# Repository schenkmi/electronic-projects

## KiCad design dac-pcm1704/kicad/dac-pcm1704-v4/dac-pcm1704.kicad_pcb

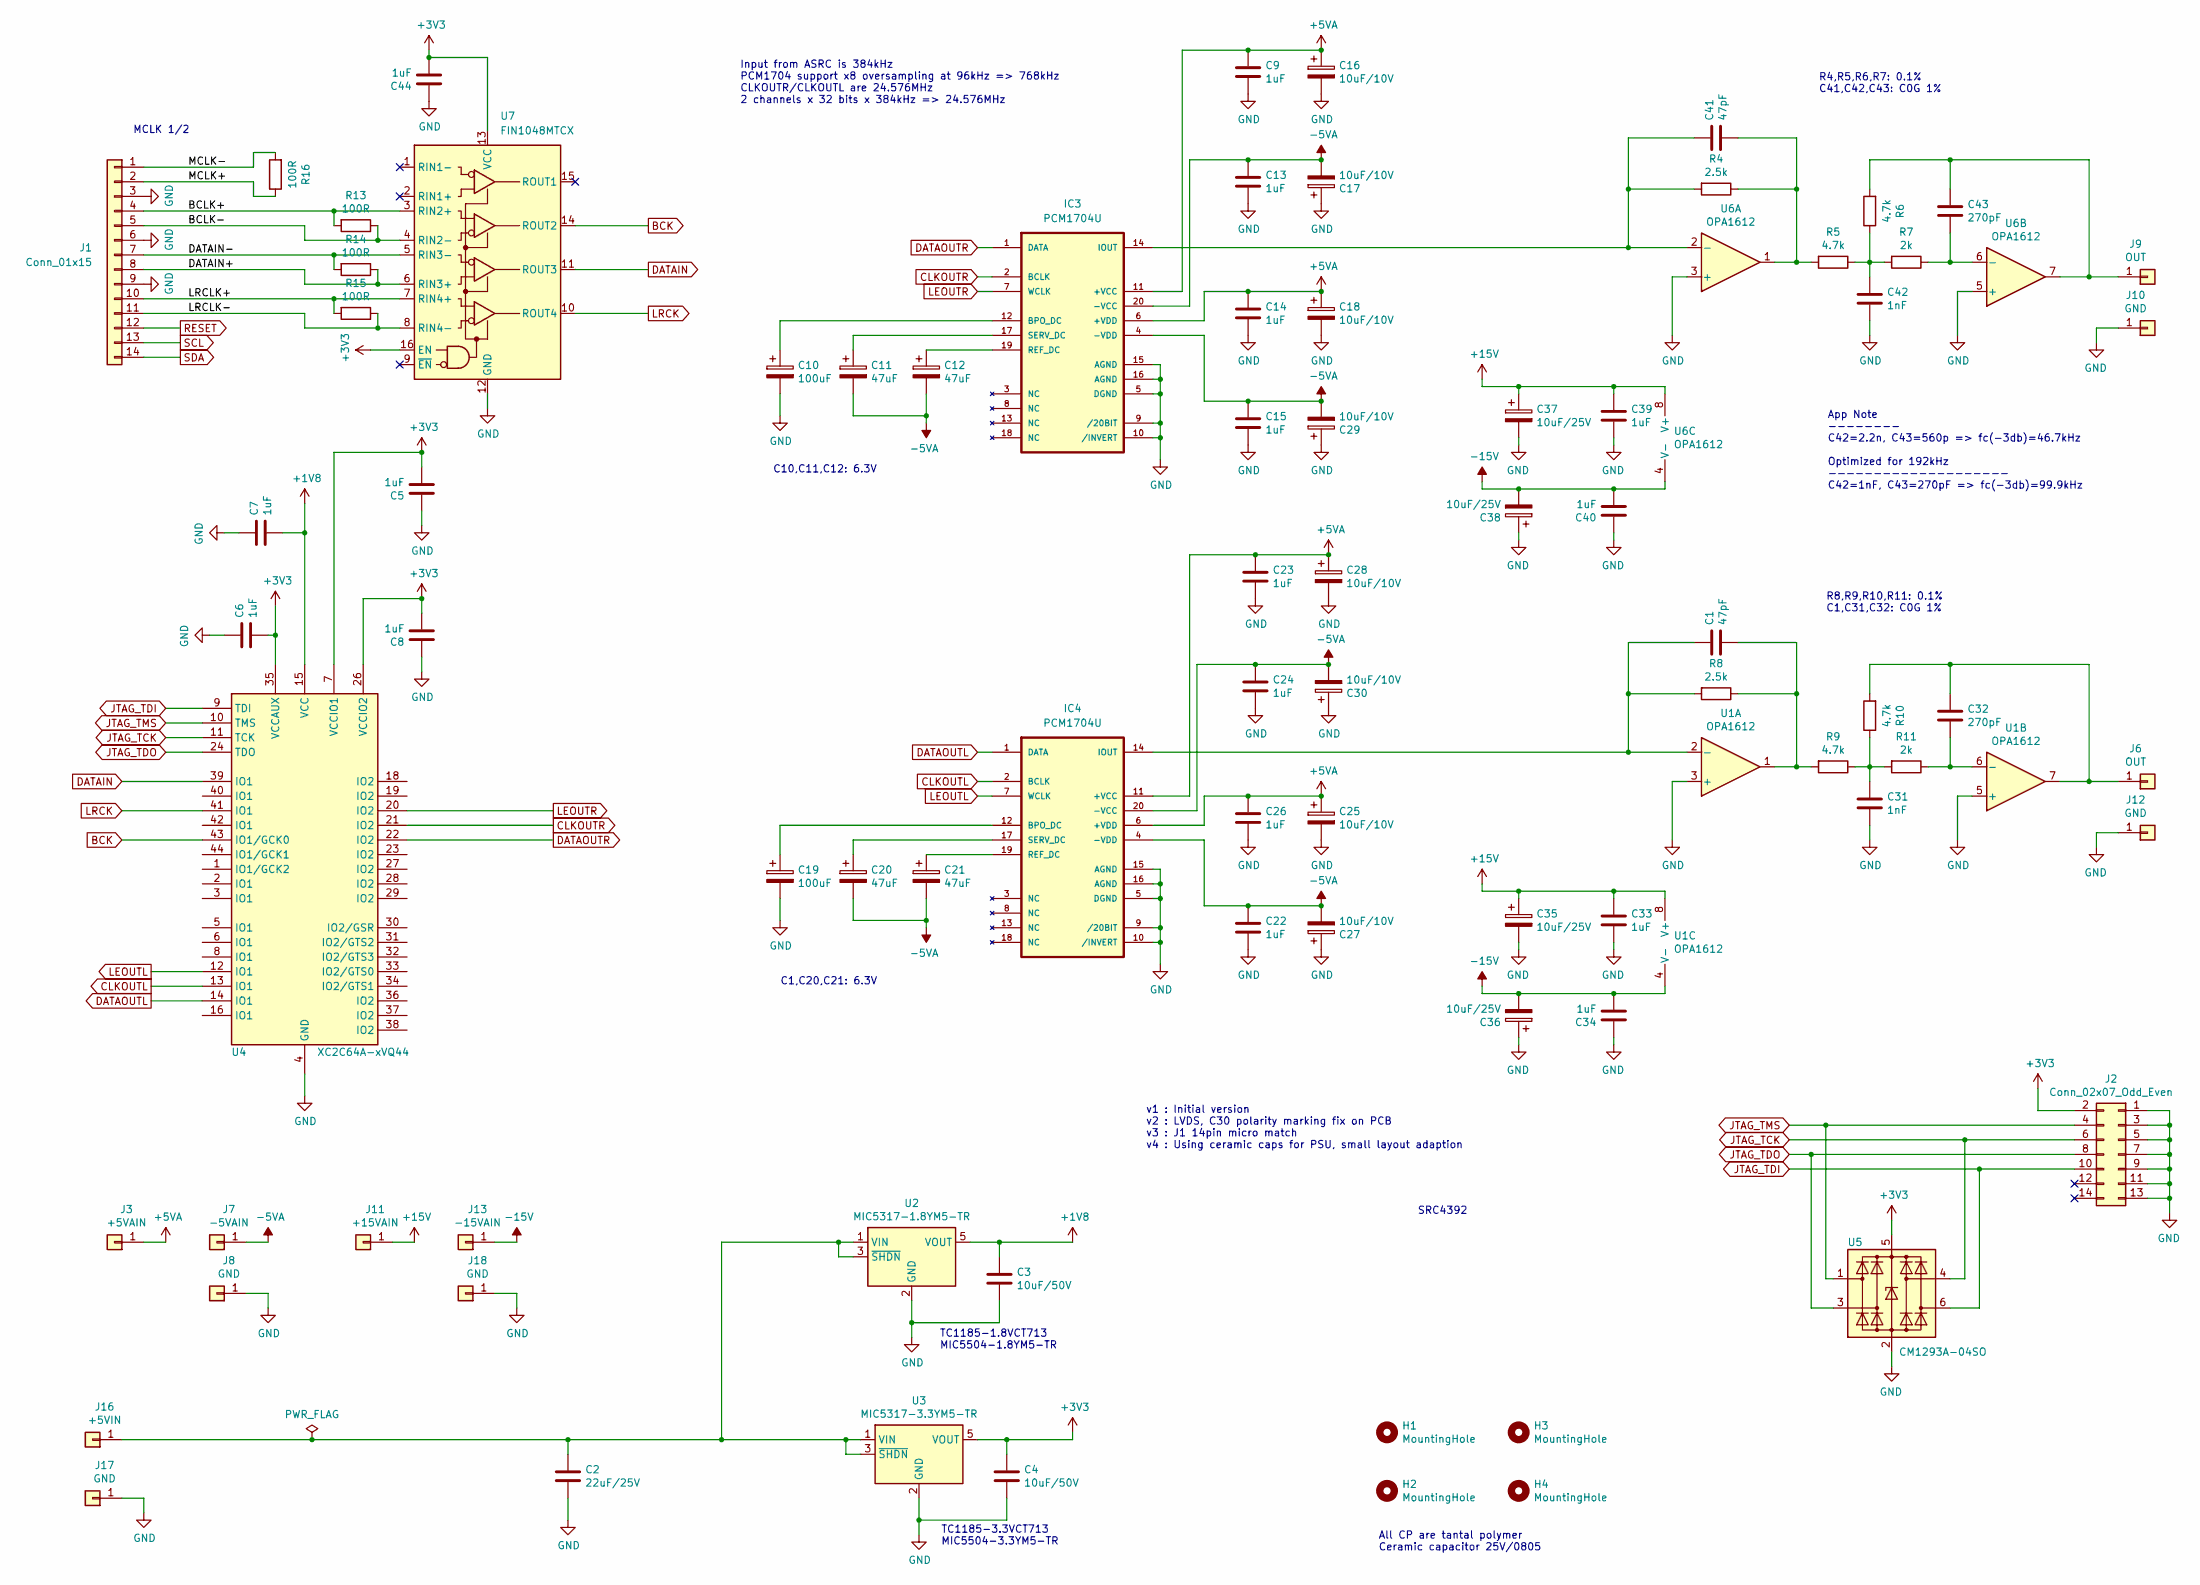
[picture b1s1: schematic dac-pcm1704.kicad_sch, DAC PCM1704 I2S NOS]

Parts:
C1, C41: 47pF; C_0805_2012Metric_Pad1.18x1.45mm_HandSolder
C2: 22uF/25V; C_1210_3225Metric_Pad1.33x2.70mm_HandSolder
C3, C4: 10uF/50V; C_1206_3216Metric_Pad1.33x1.80mm_HandSolder
C5, C6, C7, C8, C44: 1uF; C_0603_1608Metric_Pad1.08x0.95mm_HandSolder
C9, C13, C14, C15, C22, C23, C24, C26, C33, C34, C39, C40: 1uF; C_0805_2012Metric_Pad1.18x1.45mm_HandSolder
C10, C19: 100uF; C_1206_3216Metric_Pad1.33x1.80mm_HandSolder
C11, C12, C20, C21: 47uF; C_1206_3216Metric_Pad1.33x1.80mm_HandSolder
C16, C17, C18, C25, C27, C28, C29, C30: 10uF/10V; C_1206_3216Metric_Pad1.33x1.80mm_HandSolder
C31, C42: 1nF; C_0805_2012Metric_Pad1.18x1.45mm_HandSolder
C32, C43: 270pF; C_0805_2012Metric_Pad1.18x1.45mm_HandSolder
C35, C36, C37, C38: 10uF/25V; C_1206_3216Metric_Pad1.33x1.80mm_HandSolder
H1, H2, H3, H4: MountingHole; MountingHole_3.2mm_M3
IC3, IC4: PCM1704U; SO-20_5.3x12.6mm_P1.27mm; MPN PCM1702P-J
J1: Conn_01x15; TE_Micro-MaTch_1-215079-4_2x07_P1.27mm_Vertical
J2: Conn_02x07_Odd_Even; PinHeader_2x07_P2.00mm_Vertical
J3: +5VAIN; Pin_D1.0mm_L10.0mm
J6, J9: OUT; Pin_D1.0mm_L10.0mm
J7: -5VAIN; Pin_D1.0mm_L10.0mm
J8, J10, J12, J17, J18: GND; Pin_D1.0mm_L10.0mm
J11: +15VAIN; Pin_D1.0mm_L10.0mm
J13: -15VAIN; Pin_D1.0mm_L10.0mm
J16: +5VIN; Pin_D1.0mm_L10.0mm
R4, R8: 2.5k; R_0805_2012Metric_Pad1.20x1.40mm_HandSolder
R5, R6, R9, R10: 4.7k; R_0805_2012Metric_Pad1.20x1.40mm_HandSolder
R7, R11: 2k; R_0805_2012Metric_Pad1.20x1.40mm_HandSolder
R13, R14, R15, R16: 100R; R_0402_1005Metric_Pad0.72x0.64mm_HandSolder
U1, U6: OPA1612; SOIC-8_3.9x4.9mm_P1.27mm
U2: MIC5317-1.8YM5-TR; SOT-23-5
U3: MIC5317-3.3YM5-TR; SOT-23-5
U4: XC2C64A-xVQ44; TQFP-44_10x10mm_P0.8mm
U5: CM1293A−04SO; SC-74-6_1.55x2.9mm_P0.95mm
U7: FIN1048MTCX; TSSOP-16_4.4x5mm_P0.65mm; Part Number FIN1047MTCX

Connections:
+1V8: C3.1, C7.2, U2.5 (VOUT), U4.15 (VCC)
+3V3: C4.1, C5.2, C6.2, C8.2, C44.2, J2.2, U3.5 (VOUT), U4.7 (VCCIO1), U4.26 (VCCIO2), U4.35 (VCCAUX), U5.5 (VBUS), U7.13 (VCC), U7.16 (EN)
+5VA: C9.1, C14.1, C16.1, C18.1, C23.1, C25.1, C26.1, C28.1, IC3.6 (+VDD), IC3.11 (+VCC), IC4.6 (+VDD), IC4.11 (+VCC), J3.1
+15V: C33.1, C35.1, C37.1, C39.1, J11.1, U1.8 (V+), U6.8 (V+)
-5VA: C11.2, C12.2, C13.1, C15.1, C17.2, C20.2, C21.2, C22.1, C24.1, C27.2, C29.2, C30.2, IC3.4 (-VDD), IC3.20 (-VCC), IC4.4 (-VDD), IC4.20 (-VCC), J7.1
-15V: C34.2, C36.2, C38.2, C40.2, J13.1, U1.4 (V-), U6.4 (V-)
/BCLK+: J1.4, R13.2, U7.3 (RIN2+)
/BCLK-: J1.5, R13.1, U7.4 (RIN2-)
/DATAIN+: J1.8, R14.1, U7.6 (RIN3+)
/DATAIN-: J1.7, R14.2, U7.5 (RIN3-)
/LRCLK+: J1.10, R15.2, U7.7 (RIN4+)
/LRCLK-: J1.11, R15.1, U7.8 (RIN4-)
/MCLK+: J1.2, R16.1
/MCLK-: J1.1, R16.2
BCK: U4.43 (IO1/GCK0), U7.14 (ROUT2)
CLKOUTL: IC4.2 (BCLK), U4.13 (IO1)
CLKOUTR: IC3.2 (BCLK), U4.21 (IO2)
DATAIN: U4.39 (IO1), U7.11 (ROUT3)
DATAOUTL: IC4.1 (DATA), U4.14 (IO1)
DATAOUTR: IC3.1 (DATA), U4.22 (IO2)
GND: C2.2, C3.2, C4.2, C5.1, C6.1, C7.1, C8.1, C9.2, C10.2, C13.2, C14.2, C15.2, C16.2, C17.1, C18.2, C19.2, C22.2, C23.2, C24.2, C25.2, C26.2, C27.1, C28.2, C29.1, C30.1, C31.2, C33.2, C34.1, C35.2, C36.1, C37.2, C38.1, C39.2, C40.1, C42.2, C44.1, IC3.5 (DGND), IC3.9 (/20BIT), IC3.10 (/INVERT), IC3.15 (AGND), IC3.16 (AGND), IC4.5 (DGND), IC4.9 (/20BIT), IC4.10 (/INVERT), IC4.15 (AGND), IC4.16 (AGND), J1.3, J1.6, J1.9, J2.1, J2.3, J2.5, J2.7, J2.9, J2.11, J2.13, J8.1, J10.1, J12.1, J17.1, J18.1, U1.3 (+), U1.5 (+), U2.2 (GND), U3.2 (GND), U4.4 (GND), U4.17 (GND), U4.25 (GND), U5.2 (GND), U6.3 (+), U6.5 (+), U7.12 (GND)
JTAG_TCK: J2.6, U4.11 (TCK), U5.4 (I/O3)
JTAG_TDI: J2.10, U4.9 (TDI), U5.6 (I/O4)
JTAG_TDO: J2.8, U4.24 (TDO), U5.3 (I/O2)
JTAG_TMS: J2.4, U4.10 (TMS), U5.1 (I/O1)
LEOUTL: IC4.7 (WCLK), U4.12 (IO1)
LEOUTR: IC3.7 (WCLK), U4.20 (IO2)
LRCK: U4.41 (IO1), U7.10 (ROUT4)
unnamed: C1.2, R8.1, R9.2, U1.1
unnamed: C31.1, R9.1, R10.1, R11.2
unnamed: C41.2, R4.1, R5.2, U6.1
unnamed: C42.1, R5.1, R6.1, R7.2
unnamed: C10.1, IC3.12 (BPO_DC)
unnamed: C41.1, IC3.14 (IOUT), R4.2, U6.2 (-)
unnamed: C12.1, IC3.19 (REF_DC)
unnamed: C11.1, IC3.17 (SERV_DC)
unnamed: C19.1, IC4.12 (BPO_DC)
unnamed: C1.1, IC4.14 (IOUT), R8.2, U1.2 (-)
unnamed: C21.1, IC4.19 (REF_DC)
unnamed: C20.1, IC4.17 (SERV_DC)
unnamed: C32.1, J6.1, R10.2, U1.7
unnamed: C43.1, J9.1, R6.2, U6.7
unnamed: C2.1, J16.1, U2.1 (VIN), U2.3 (~SHDN), U3.1 (VIN), U3.3 (~SHDN)
unnamed: C32.2, R11.1, U1.6 (-)
unnamed: C43.2, R7.1, U6.6 (-)
RESET: J1.12
SCL: J1.13
SDA: J1.14

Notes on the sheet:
App Note -------- C42=2.2n, C43=560p => fc(-3db)=46.7kHz Optimized for 192kHz -------------------- C42=1nF, C43=270pF => fc(-3db)=99.9kHz
All CP are tantal polymer Ceramic capacitor 25V/0805
R4,R5,R6,R7: 0.1% C41,C42,C43: C0G 1%
v1 : Initial version v2 : LVDS, C30 polarity marking fix on PCB v3 : J1 14pin micro match v4 : Using ceramic caps for PSU, small layout adaption
SRC4392
C1,C20,C21: 6.3V
TC1185-3.3VCT713 MIC5504-3.3YM5-TR
C10,C11,C12: 6.3V
R8,R9,R10,R11: 0.1% C1,C31,C32: C0G 1%
Input from ASRC is 384kHz PCM1704 support x8 oversampling at 96kHz => 768kHz CLKOUTR/CLKOUTL are 24.576MHz 2 channels x 32 bits x 384kHz => 24.576MHz
MCLK 1/2
TC1185-1.8VCT713 MIC5504-1.8YM5-TR

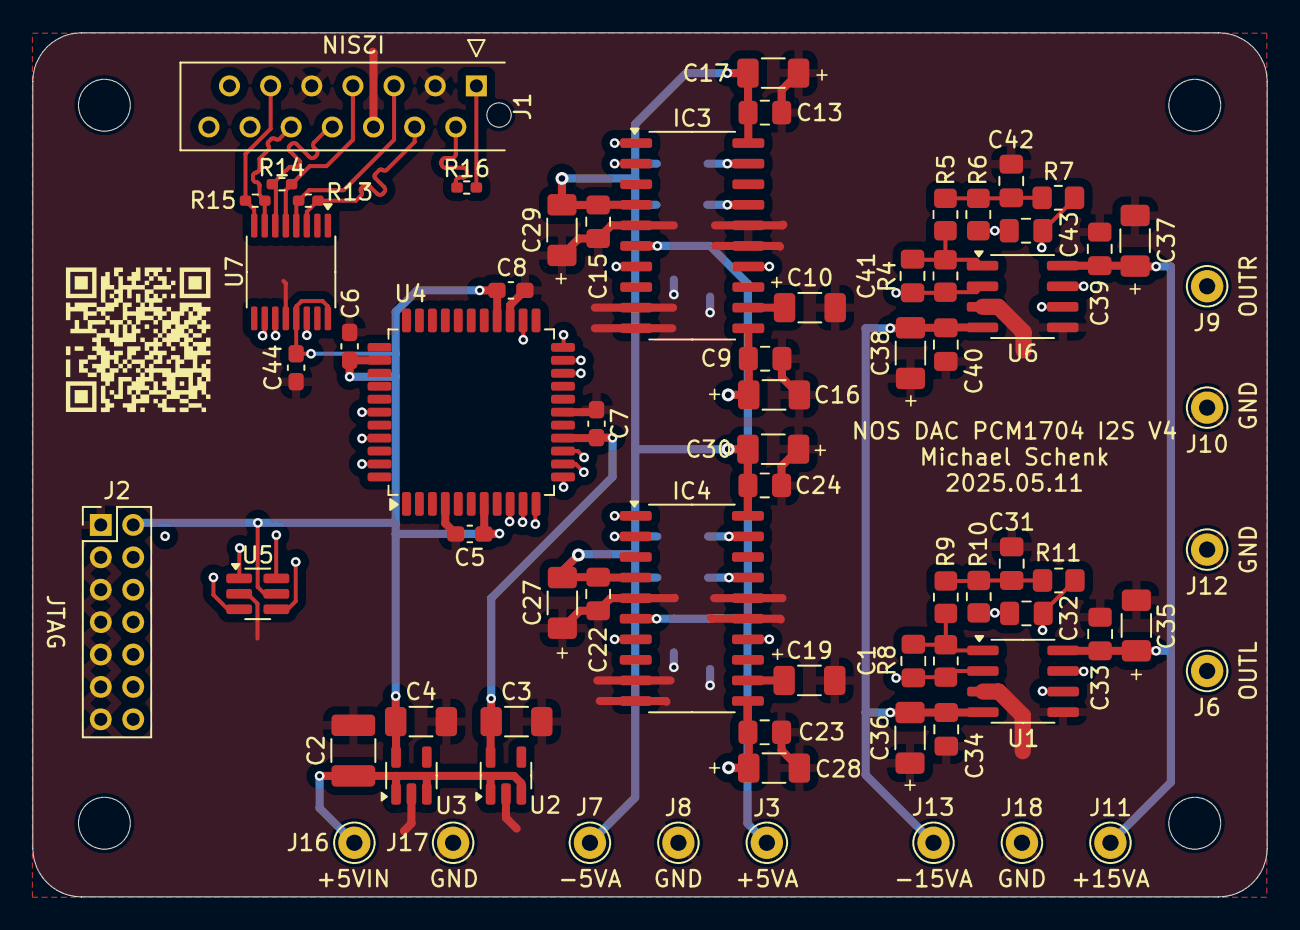
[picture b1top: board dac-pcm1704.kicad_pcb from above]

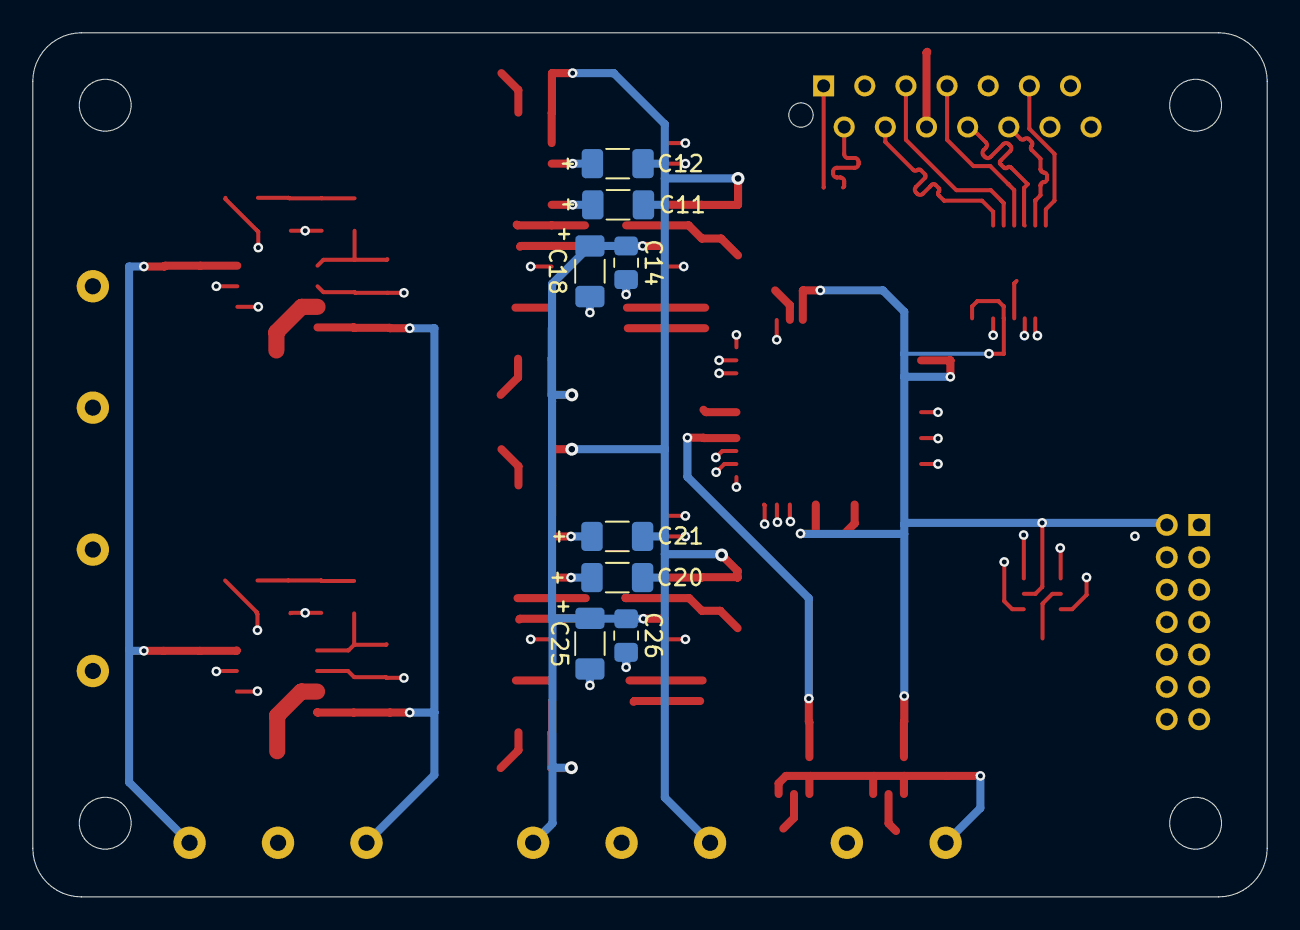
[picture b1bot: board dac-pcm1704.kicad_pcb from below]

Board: 4 copper layers, 76.2 x 53.3 mm, 83 parts (8 on the bottom side), 45 nets.

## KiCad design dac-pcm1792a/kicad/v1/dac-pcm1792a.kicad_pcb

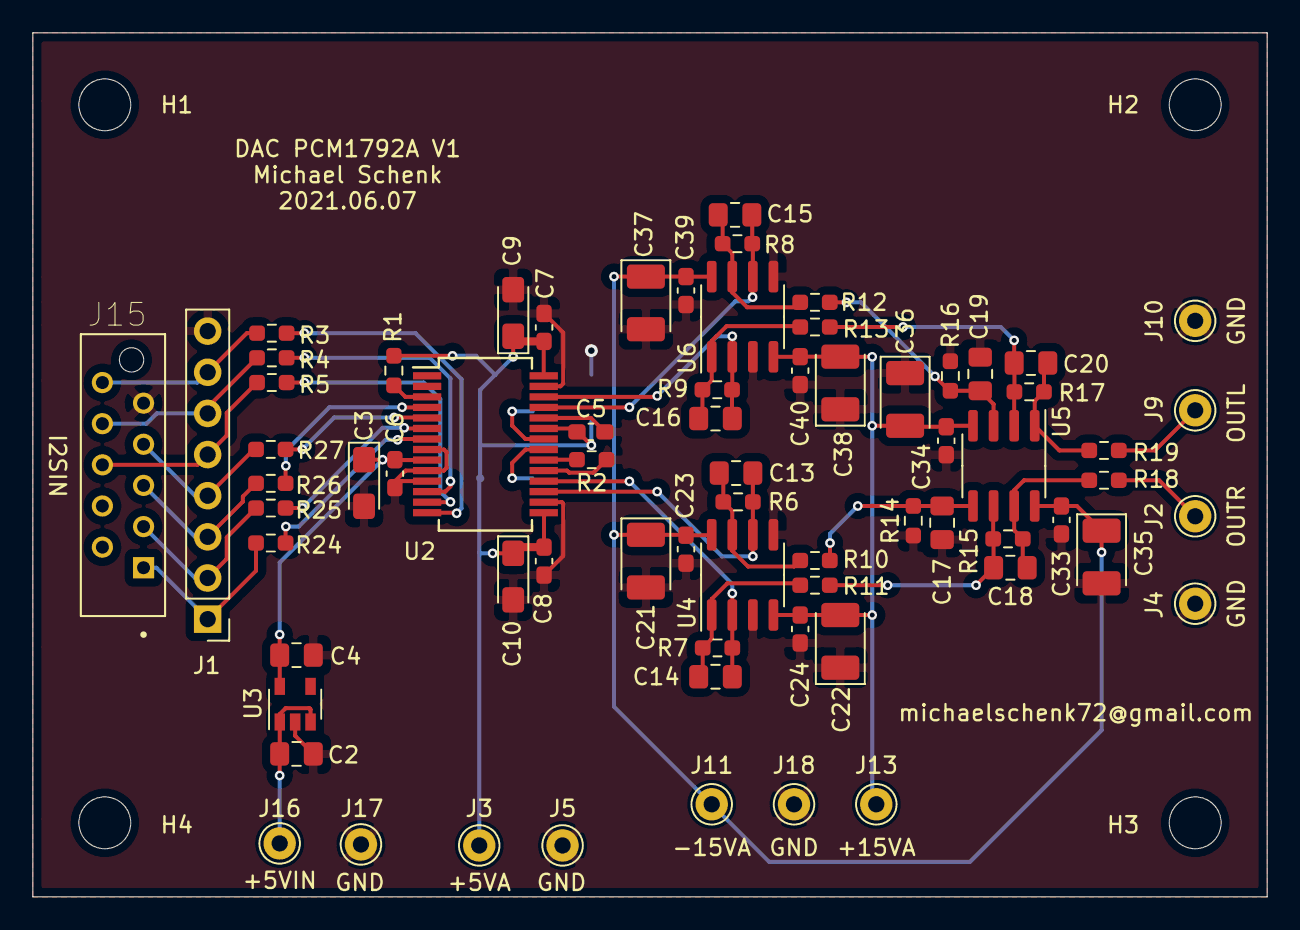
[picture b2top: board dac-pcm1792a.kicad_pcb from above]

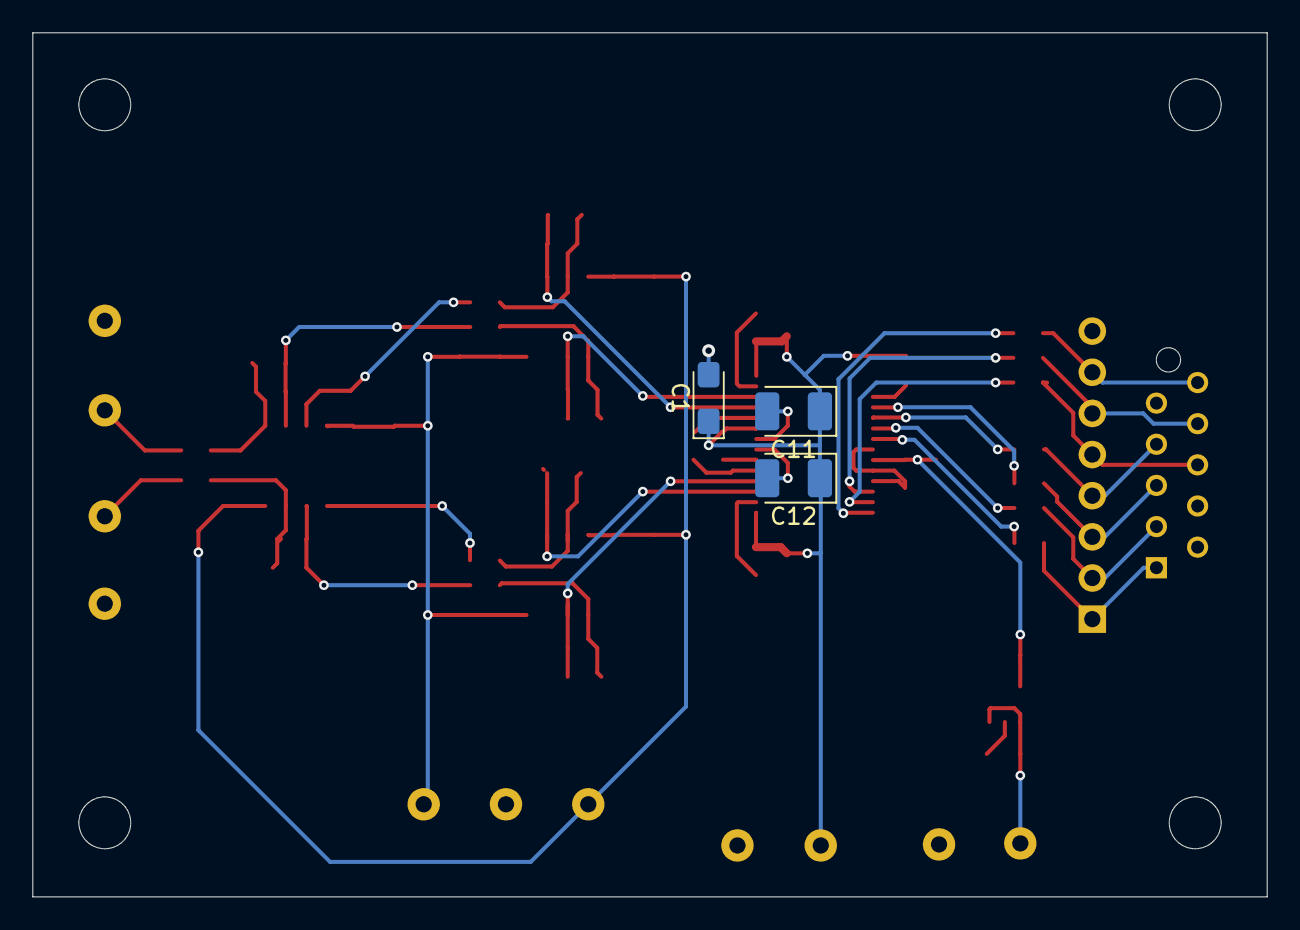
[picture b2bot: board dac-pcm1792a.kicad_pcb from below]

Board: 2 copper layers, 76.2 x 53.3 mm, 77 parts (3 on the bottom side), 40 nets.

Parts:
C1, C3, C9, C10: 10uF/10V; CP_EIA-3216-18_Kemet-A_Pad1.58x1.35mm_HandSolder
C2, C4: 10uF; C_0805_2012Metric_Pad1.18x1.45mm_HandSolder
C5, C6, C7, C8, C23, C24, C33, C34, C39, C40: 100nF; C_0603_1608Metric_Pad1.08x0.95mm_HandSolder
C11, C12: 47uF/10V; CP_EIA-3528-12_Kemet-T_Pad1.50x2.35mm_HandSolder
C13, C14, C15, C16: 2200pF/2%; C_0805_2012Metric_Pad1.18x1.45mm_HandSolder
C17, C18, C19, C20: 2700pF/2%; C_0805_2012Metric_Pad1.18x1.45mm_HandSolder
C21, C22, C35, C36, C37, C38: 10uF/25V; CP_EIA-3528-21_Kemet-B_Pad1.50x2.35mm_HandSolder
H1, H2, H3, H4: MountingHole; MountingHole_3.2mm_M3
J1: DEBUG; PinHeader_1x08_P2.54mm_Vertical
J2: OUTR; Pin_D1.0mm_L10.0mm
J3: +5VAIN; Pin_D1.0mm_L10.0mm
J4: GNDR; Pin_D1.0mm_L10.0mm
J5: +5VAGND; Pin_D1.0mm_L10.0mm
J9: OUTL; Pin_D1.0mm_L10.0mm
J10: GNDL; Pin_D1.0mm_L10.0mm
J11: +15VAIN; Pin_D1.0mm_L10.0mm
J13: -15VAIN; Pin_D1.0mm_L10.0mm
J15: A; TE_CONN_RCPT_10POS_0.1_TIN_PCB
J16: +5VIN; Pin_D1.0mm_L10.0mm
J17, J18: GND; Pin_D1.0mm_L10.0mm
R1: 4k7; R_0603_1608Metric_Pad0.98x0.95mm_HandSolder
R2: 10k; R_0603_1608Metric_Pad0.98x0.95mm_HandSolder
R3, R4, R5, R24, R25, R26, R27: 33R; R_0603_1608Metric_Pad0.98x0.95mm_HandSolder
R6, R7, R8, R9: 750R/0.1%; R_0603_1608Metric_Pad0.98x0.95mm_HandSolder
R10, R11, R12, R13: 560R/0.1%; R_0603_1608Metric_Pad0.98x0.95mm_HandSolder
R14, R15, R16, R17: 270R/0.1%; R_0603_1608Metric_Pad0.98x0.95mm_HandSolder
R18, R19: 100R/0.1%; R_0603_1608Metric_Pad0.98x0.95mm_HandSolder
U2: PCM1792A; SSOP-28_5.3x10.2mm_P0.65mm
U3: TC1185-3.3VCT713; SOT-23-5
U4, U5, U6: OPA1612; SOIC-8_3.9x4.9mm_P1.27mm

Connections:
+3V3: C3.1, C4.1, C6.1, U2.9, U3.5
+5VA: C1.1, C5.1, C7.1, C8.1, C9.1, C10.1, C11.1, C12.1, J3.1, R1.1, U2.15, U2.23, U2.28
+15V: C21.1, C23.1, C33.1, C35.1, C37.1, C39.1, J11.1, U4.8, U5.8, U6.8
-15V: C22.2, C24.2, C34.2, C36.2, C38.2, C40.2, J13.1, U4.4, U5.4, U6.4
BCK: R25.2, U2.6
DATAIN: R27.2, U2.5
GND: C1.2, C2.2, C3.2, C4.2, C5.2, C6.2, C7.2, C8.2, C9.2, C10.2, C17.1, C19.1, C21.2, C22.1, C23.2, C24.1, C33.2, C34.1, C35.2, C36.1, C37.2, C38.1, C39.2, C40.1, J1.8, J4.1, J5.1, J10.1, J15.9, J17.1, J18.1, R2.1, R14.1, R16.1, U2.8, U2.10, U2.11, U2.16, U2.19, U2.24, U2.27, U3.2, U4.3, U4.5, U6.3, U6.5
LRCK: R26.2, U2.4
MCLK: R24.2, U2.7
unnamed: C2.1, J16.1, U3.1, U3.3
unnamed: C11.2, U2.22
unnamed: C12.2, U2.21
unnamed: C13.1, R6.1, R10.2, U4.7
unnamed: C13.2, R6.2, U2.17, U4.6
unnamed: C14.1, R7.1, R11.2, U4.1
unnamed: C14.2, R7.2, U2.18, U4.2
unnamed: C15.1, R8.1, R12.2, U6.7
unnamed: C15.2, R8.2, U2.25, U6.6
unnamed: C16.1, R9.1, R13.2, U6.1
unnamed: C16.2, R9.2, U2.26, U6.2
unnamed: C17.2, R10.1, R14.2, U5.5
unnamed: C18.1, R11.1, R15.1, U5.6
unnamed: C18.2, R15.2, R18.2, U5.7
unnamed: C19.2, R12.1, R16.2, U5.3
unnamed: C20.1, R13.1, R17.1, U5.2
unnamed: C20.2, R17.2, R19.2, U5.1
unnamed: J1.1, J15.1, R24.1
unnamed: J1.2, J15.3, R25.1
unnamed: J1.3, J15.5, R26.1
unnamed: J1.4, J15.7, R27.1
unnamed: J1.5, J15.6, R5.2
unnamed: J1.6, J15.8, R4.2
unnamed: J1.7, J15.10, R3.2
unnamed: J2.1, R18.1
unnamed: J9.1, R19.1
unnamed: R1.2, U2.3
unnamed: R2.2, U2.20
RESET: R3.1, U2.14
SCL: R4.1, U2.12
SDA: R5.1, U2.13
